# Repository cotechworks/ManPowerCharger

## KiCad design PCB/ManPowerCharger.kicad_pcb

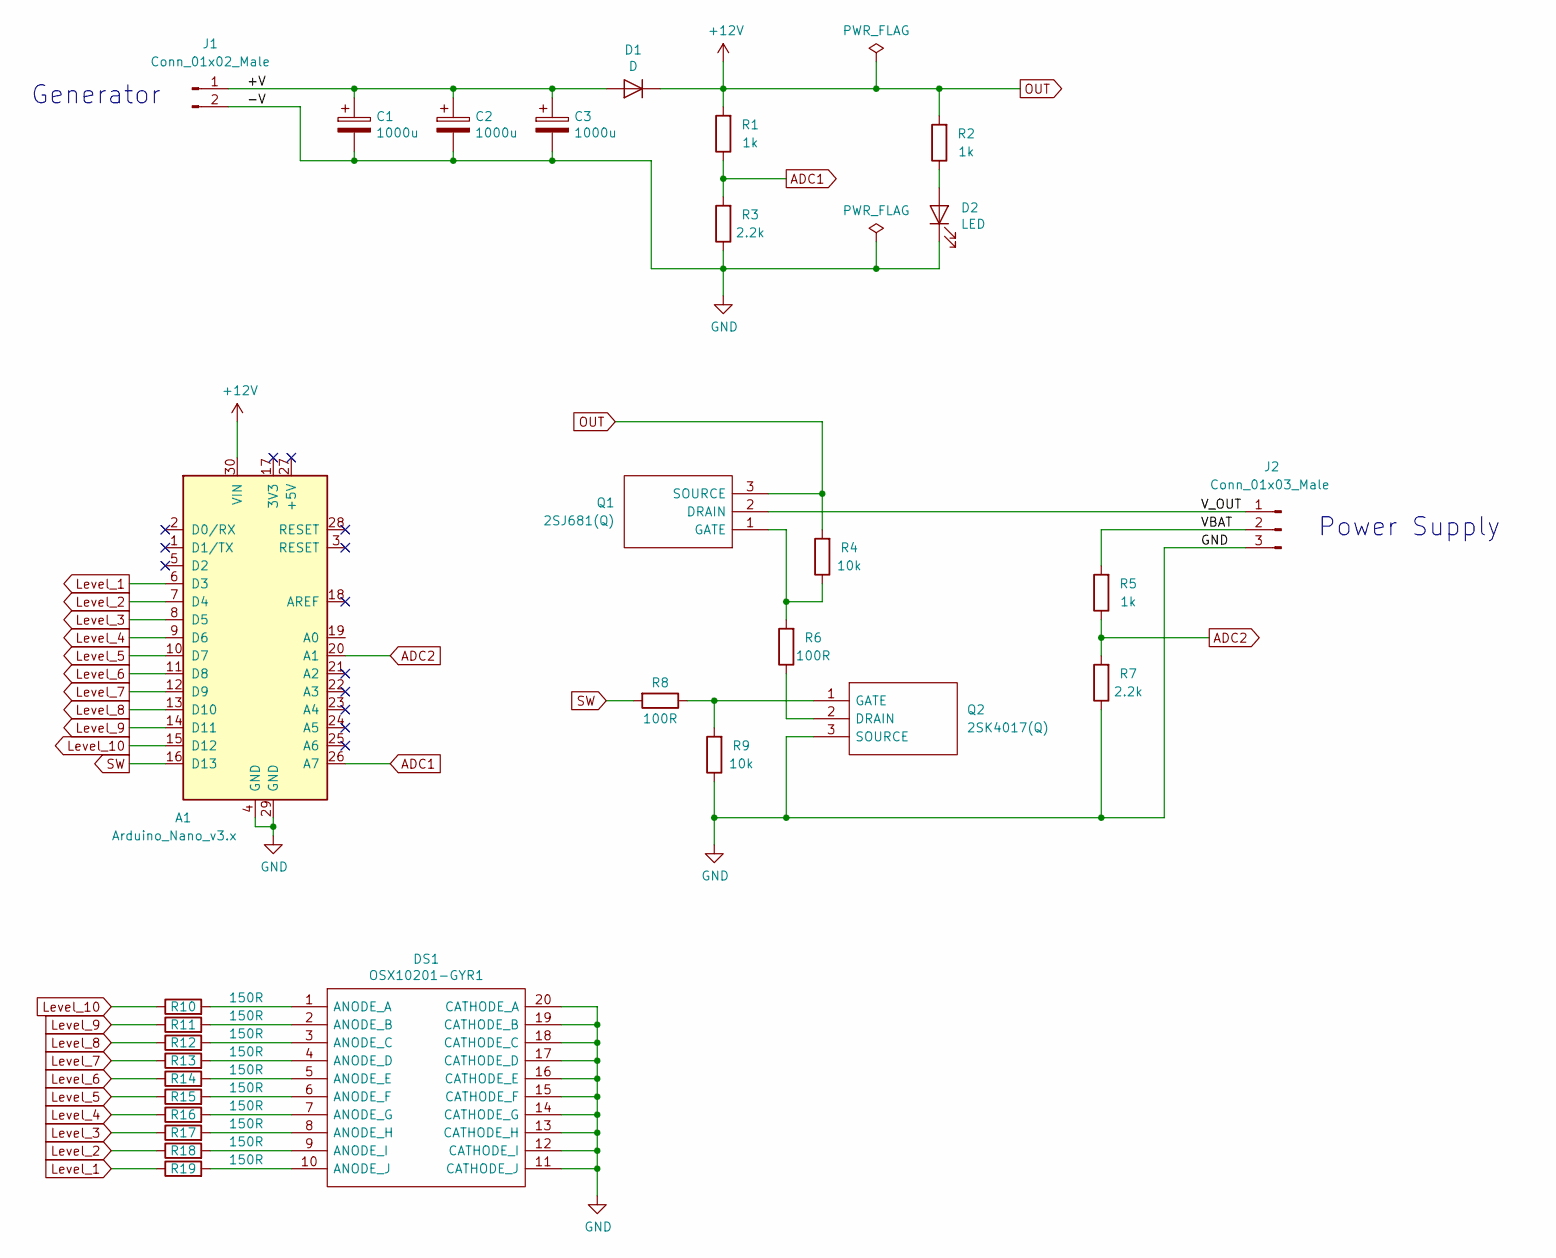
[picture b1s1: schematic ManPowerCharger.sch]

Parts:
A1: Arduino_Nano_v3.x; Arduino_Nano
C1, C2, C3: 1000u; CP_Radial_D16.0mm_P7.50mm
D1: D; D_A-405_P7.62mm_Horizontal
D2: LED; LED_D3.0mm
DS1: OSX10201-GYR1; DIPS760W45P254L2550H815Q20N; Manufacturer_Part_Number OSX10201-GYR1
J1: Conn_01x02_Male; PinHeader_1x02_P2.54mm_Vertical
J2: Conn_01x03_Male; PinHeader_1x03_P2.54mm_Vertical
Q1: 2SJ681(Q); TO230P250X650X900-3P; Manufacturer_Part_Number 2SJ681(Q)
Q2: 2SK4017(Q); TO230P250X650X900-3P; Manufacturer_Part_Number 2SK4017(Q)
R1, R2, R5: 1k; R_Axial_DIN0204_L3.6mm_D1.6mm_P7.62mm_Horizontal
R3, R7: 2.2k; R_Axial_DIN0204_L3.6mm_D1.6mm_P7.62mm_Horizontal
R4, R9: 10k; R_Axial_DIN0204_L3.6mm_D1.6mm_P7.62mm_Horizontal
R6, R8: 100R; R_Axial_DIN0204_L3.6mm_D1.6mm_P7.62mm_Horizontal
R10, R11, R12, R13, R14, R15, R16, R17, R18, R19: 150R; R_Axial_DIN0204_L3.6mm_D1.6mm_P7.62mm_Horizontal

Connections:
/+V: C1.1, C2.1, C3.1, D1.2 (A), J1.1
/VBAT: J2.2, R5.2
/V_OUT: J2.1, Q1.2 (DRAIN)
ADC1: A1.26 (A7), R1.1, R3.2
ADC2: A1.20 (A1), R5.1, R7.2
GND: A1.4 (GND), A1.29 (GND), C1.2, C2.2, C3.2, D2.1 (K), DS1.11 (CATHODE_J), DS1.12 (CATHODE_I), DS1.13 (CATHODE_H), DS1.14 (CATHODE_G), DS1.15 (CATHODE_F), DS1.16 (CATHODE_E), DS1.17 (CATHODE_D), DS1.18 (CATHODE_C), DS1.19 (CATHODE_B), DS1.20 (CATHODE_A), J1.2, J2.3, Q2.3 (SOURCE), R3.1, R7.1, R9.1
Level_1: A1.6 (D3), R19.1
Level_2: A1.7 (D4), R18.1
Level_3: A1.8 (D5), R17.1
Level_4: A1.9 (D6), R16.1
Level_5: A1.10 (D7), R15.1
Level_6: A1.11 (D8), R14.1
Level_7: A1.12 (D9), R13.1
Level_8: A1.13 (D10), R12.1
Level_9: A1.14 (D11), R11.1
Level_10: A1.15 (D12), R10.1
unnamed: D2.2 (A), R2.1
unnamed: DS1.1 (ANODE_A), R10.2
unnamed: DS1.2 (ANODE_B), R11.2
unnamed: DS1.3 (ANODE_C), R12.2
unnamed: DS1.4 (ANODE_D), R13.2
unnamed: DS1.5 (ANODE_E), R14.2
unnamed: DS1.6 (ANODE_F), R15.2
unnamed: DS1.7 (ANODE_G), R16.2
unnamed: DS1.8 (ANODE_H), R17.2
unnamed: DS1.9 (ANODE_I), R18.2
unnamed: DS1.10 (ANODE_J), R19.2
unnamed: Q1.1 (GATE), R4.1, R6.2
unnamed: Q2.1 (GATE), R8.1, R9.2
unnamed: Q2.2 (DRAIN), R6.1
OUT: A1.30 (VIN), D1.1 (K), Q1.3 (SOURCE), R1.2, R2.2, R4.2
SW: A1.16 (D13), R8.2

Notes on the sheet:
Generator
Power Supply

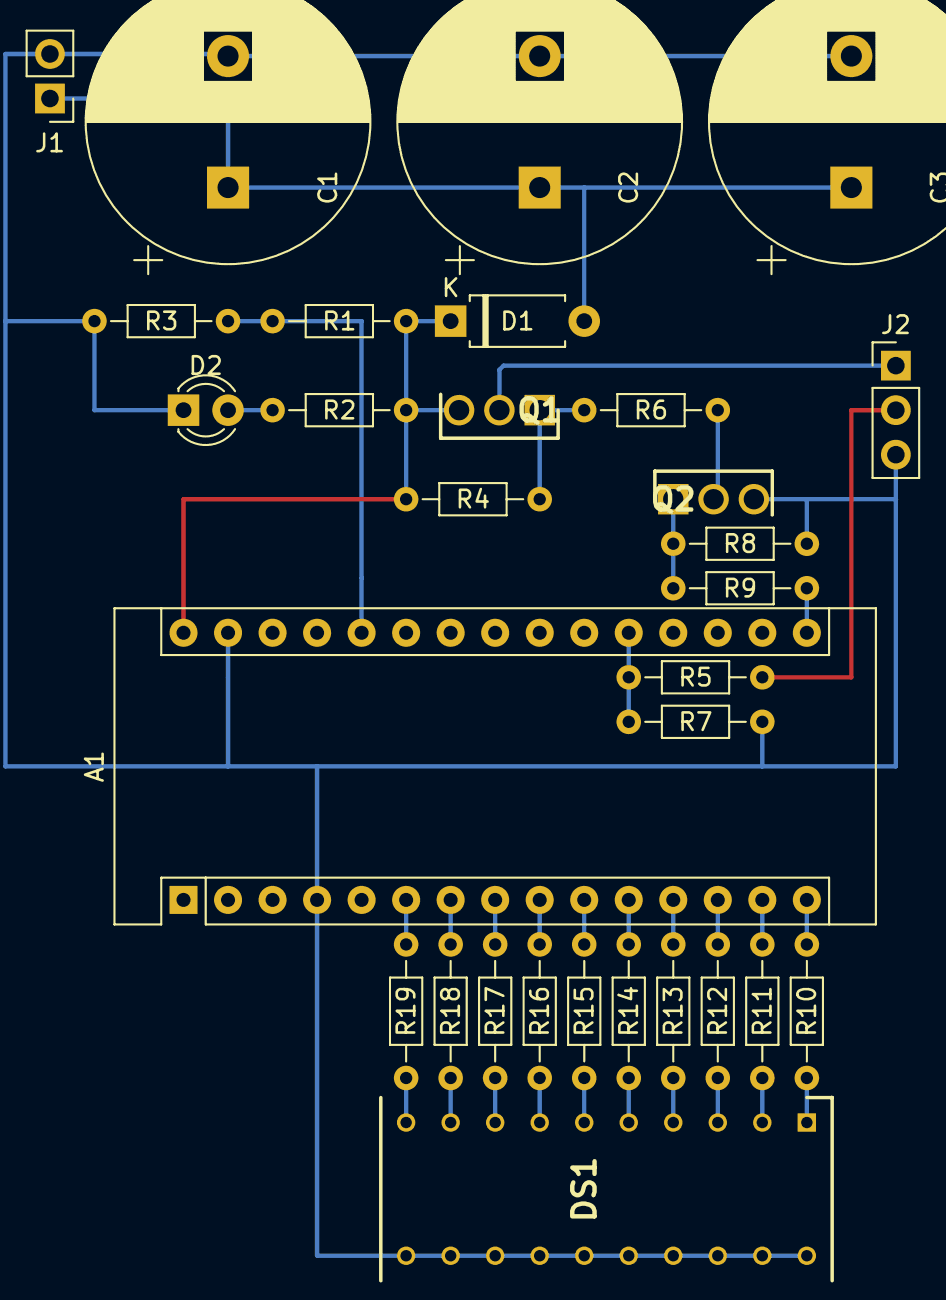
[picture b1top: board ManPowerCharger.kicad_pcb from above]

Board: 2 copper layers, 30 parts (0 on the bottom side), 32 nets.

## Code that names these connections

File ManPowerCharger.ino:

#include <TimerOne.h>

#define LEVEL_1 3
#define LEVEL_2 4
#define LEVEL_3 5
#define LEVEL_4 6
#define LEVEL_5 7
#define LEVEL_6 8
#define LEVEL_7 9
#define LEVEL_8 10
#define LEVEL_9 11
#define LEVEL_10 12
#define ADC1_PIN 7
#define ADC2_PIN 0
#define SW_PIN 13

#define ADC1_LOWER_VOLT 8.7   /* 充電開始電圧 */
#define ADC2_LOWER_VOLT 7.4   /* 残量計　下限 */
#define ADC2_UPPER_VOLT 8.4   /* 残量計　上限 */
#define ADC_CV 1.135          /* ADCの補正係数 */

int i;
int ADC1,ADC2;
float ADC2_Spec[10] = {0};
float ADC1_Volt,ADC2_Volt;

void setup() {
  Serial.begin(9600);
  pinMode(LEVEL_1, OUTPUT);
  pinMode(LEVEL_2, OUTPUT);
  pinMode(LEVEL_3, OUTPUT);
  pinMode(LEVEL_4, OUTPUT);
  pinMode(LEVEL_5, OUTPUT);
  pinMode(LEVEL_6, OUTPUT);
  pinMode(LEVEL_7, OUTPUT);
  pinMode(LEVEL_8, OUTPUT);
  pinMode(LEVEL_9, OUTPUT);
  pinMode(LEVEL_10, OUTPUT);
  pinMode(SW_PIN, OUTPUT);

  for (i = 0; i < 10; i++) {
    ADC2_Spec[i] = ADC2_LOWER_VOLT + (ADC2_UPPER_VOLT - ADC2_LOWER_VOLT) * (i) / 10;
    Serial.print(ADC2_Spec[i]);
    Serial.print("\n");
  }

  Timer1.initialize(1000000); //マイクロ秒単位で設定
  Timer1.attachInterrupt(timerFire);
}

void loop() {
  /* 電圧確認 */
  ADC1 = analogRead(ADC1_PIN);
  ADC2 = analogRead(ADC2_PIN);

  ADC1_Volt = ((float)ADC1 * 5.0 * 3.2) / (1023.0) * ADC_CV;
  ADC2_Volt = ((float)ADC2 * 5.0 * 3.2) / (1023.0) * ADC_CV;

  /* 残量計 */
  digitalWrite(LEVEL_1, LOW);
  digitalWrite(LEVEL_2, LOW);
  digitalWrite(LEVEL_3, LOW);
  digitalWrite(LEVEL_4, LOW);
  digitalWrite(LEVEL_5, LOW);
  digitalWrite(LEVEL_6, LOW);
  digitalWrite(LEVEL_7, LOW);
  digitalWrite(LEVEL_8, LOW);
  digitalWrite(LEVEL_9, LOW);
  digitalWrite(LEVEL_10, LOW);
  
  digitalWrite(LEVEL_1, HIGH);
  if (ADC2_Volt > ADC2_Spec[1])digitalWrite(LEVEL_2, HIGH);
  if (ADC2_Volt > ADC2_Spec[2])digitalWrite(LEVEL_3, HIGH);
  if (ADC2_Volt > ADC2_Spec[3])digitalWrite(LEVEL_4, HIGH);
  if (ADC2_Volt > ADC2_Spec[4])digitalWrite(LEVEL_5, HIGH);
  if (ADC2_Volt > ADC2_Spec[5])digitalWrite(LEVEL_6, HIGH);
  if (ADC2_Volt > ADC2_Spec[6])digitalWrite(LEVEL_7, HIGH);
  if (ADC2_Volt > ADC2_Spec[7])digitalWrite(LEVEL_8, HIGH);
  if (ADC2_Volt > ADC2_Spec[8])digitalWrite(LEVEL_9, HIGH);
  if (ADC2_Volt > ADC2_Spec[9])digitalWrite(LEVEL_10, HIGH);

  /* 電源電圧の確認・ON/OFF制御 */
  if(ADC1_Volt >= ADC1_LOWER_VOLT){
    digitalWrite(SW_PIN, HIGH);
  }else{
    digitalWrite(SW_PIN, LOW);
  }
}

void timerFire() {  /* タイマー割込み */
  Serial.print(ADC1_Volt);
  Serial.print(",");
  Serial.print(ADC2_Volt);
  Serial.print("\n");
}

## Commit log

2019-12-29 PCB追加
2019-12-29 回路図修正（PCB未反映）
2019-12-29 回路図PDF追加
